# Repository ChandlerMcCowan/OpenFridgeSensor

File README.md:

# OpenFridgeSensor
Open source sensor and alarm system to remind you to close the fridge!

## Overview
I want to create a small sensor that lives in the fridge that can let you know when you accidentally leave the fridge door ajar. Most modern fridges come with this feature standard, but there are plenty of old fridges out there still keeping the beer cold. My goal is to have a low cost, battery powered sensor that connects wirelessy to a display that can be stuck to the fridge door with magnets. 

## Alert Types
Currently, I plan on using a small speaker to notify people that the door was left open. Other options could also include internet connectivity for when you might have just left the house after grabbing something out of the fridge. 

## Sensor Types
I plan on using a ambient light sensor to determine if the door was left open. These sensors are found in most smart phones to allow for automatically adjusting the screen's brightness. These sensors are low cost and come in small packages, perfect for a small device that shouldn't take up too much space in the fridge. 

Another idea is to add a temperature sensor to allow for alerts from loss of power or if the door is open but the light hasn't been switched on. This could be a simple thermistor, or it could be the popular DHT11 sensor, which would give humidity as well.

## Display Types
I want to explore the idea of using a small OLED or TFT display that attaches to the fridge door with magnets. This could show the current status of the sesnor, and flash for any alerts. Another idea is to include a user interface to allow for setting when to issue alerts, and what type of alerts. 

## Wireless Connectivity
I've looked at 433 Mhz in the ISM band to allow for wireless data transmission from the sensor inside the fridge to the display on the fridge door. There are plenty of small transmitter and reciever ICs. I expect to only need a transmitter for the in-fridge sensor, and just a reciever in the display. One area that I want to explore is the use of a PCB antenna instead of the common wire antenna. This will require some work, so I might fall back on the purchased antenna.

I want to explore using JSON objects to pass data from the sensor to the display.

## Battery Power
Both the sensor and the display should be batter powered. Maybe the display can have an IR sensor that detects when a person walks by to keep power consumption down. I expect to use a coincell for the in-fridge sensor, and maybe a 9V battery for the display. These will need some exploration to determine the best solution when the power consumption is calculated. 

## Enclosures
As usual, I will create some enclosures that can be 3D printed. One thing that might be interesting is to explore using epoxy or conformal coating to increase sensor robustness.

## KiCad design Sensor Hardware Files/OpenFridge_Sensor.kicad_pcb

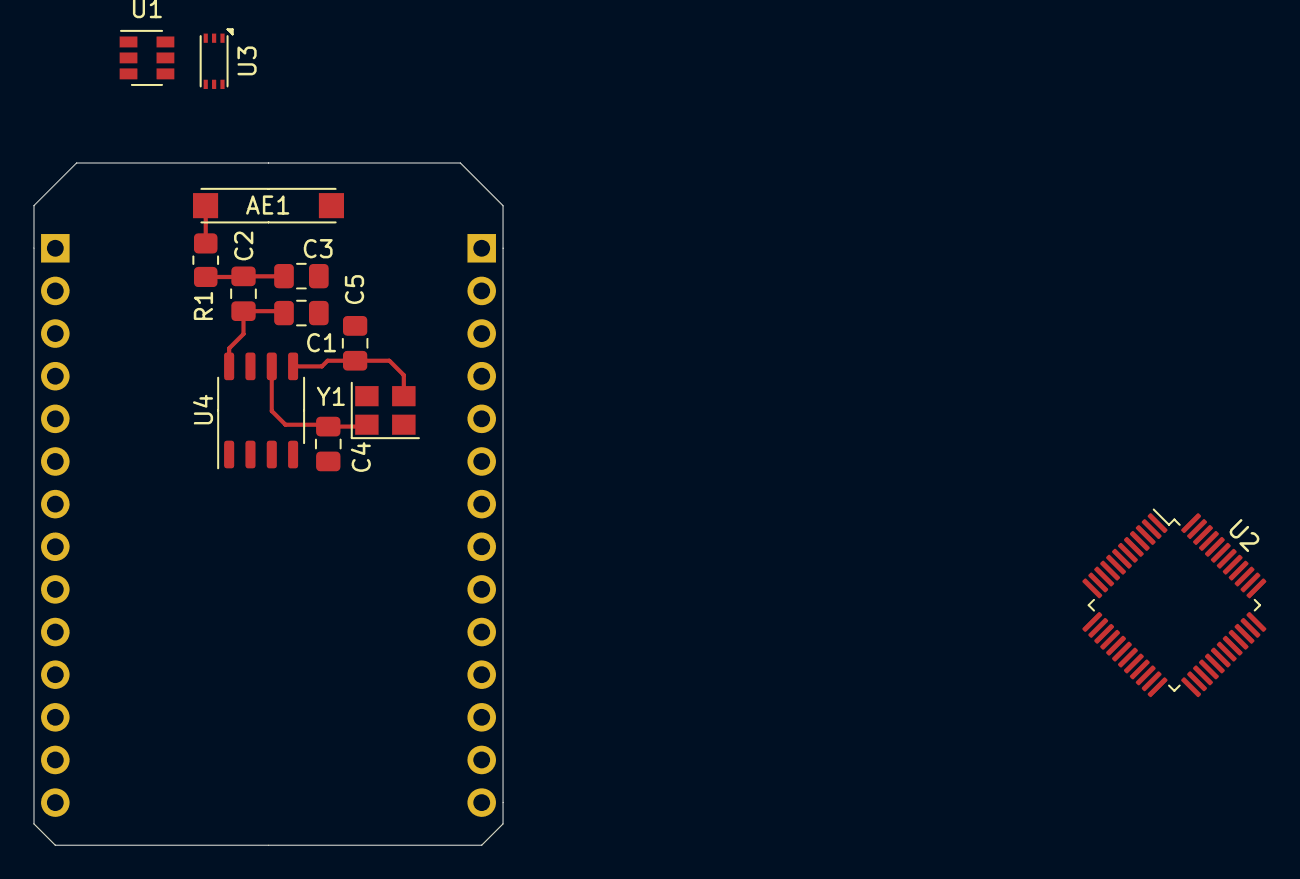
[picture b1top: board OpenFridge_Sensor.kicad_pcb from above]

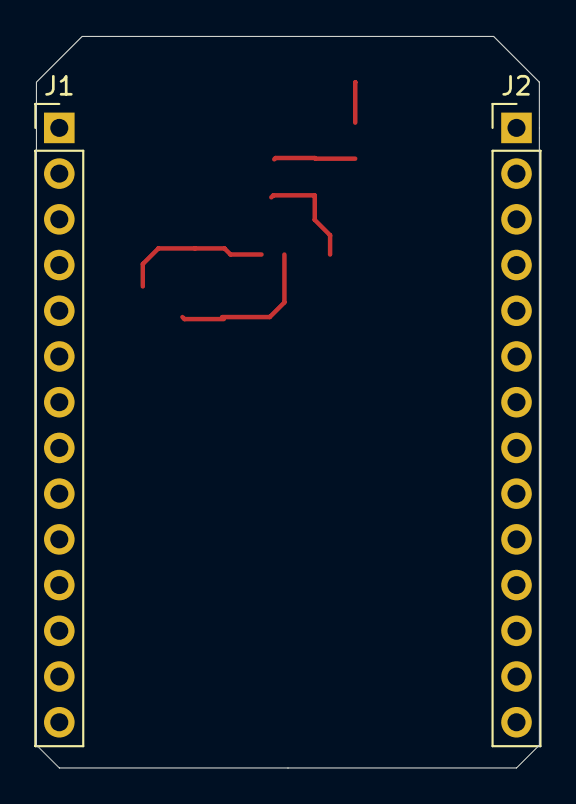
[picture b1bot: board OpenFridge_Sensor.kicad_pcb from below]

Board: 2 copper layers, 27.9 x 40.6 mm, 14 parts (2 on the bottom side), 8 nets.

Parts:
AE1: Antenna_Chip; RFANT8010080A3T
C1, C2, C3: C; C_0805_2012Metric_Pad1.18x1.45mm_HandSolder
C4, C5: 12pF; C_0805_2012Metric_Pad1.18x1.45mm_HandSolder
J1, J2: Conn_01x14; PinHeader_1x14_P2.54mm_Vertical
R1: R; R_0805_2012Metric_Pad1.20x1.40mm_HandSolder
U1: TMP101; SOT-23-6
U2: STM32F103C8Tx; LQFP-48_7x7mm_P0.5mm
U3: BH1730FVC; WSOF-6
U4: XN297LBW; SOP-8_3.9x4.9mm_P1.27mm
Y1: 16 MHz 12pF; Crystal_SMD_3225-4Pin_3.2x2.5mm

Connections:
GND: AE1.1, C1.1, C3.1, C4.1, C5.1, U4.7, Y1.2, Y1.4
I2C1_SCL: U1.1, U3.6
I2C1_SDA: U1.6, U3.4
unnamed: AE1.2, R1.1
unnamed: C1.2, C2.2, U4.8
unnamed: C2.1, C3.2, R1.2
unnamed: C4.2, U4.6, Y1.1
unnamed: C5.2, U4.5, Y1.3

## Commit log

2020-09-12 Add Sensor Hardware CAD files
2020-09-12 Add Display CAD Files
2020-09-12 Add empty Enclosure CAD Files
2020-09-12 Add License
2020-10-07 Add step up circuit
2020-10-07 Add ISM transceiver symbols and library
2020-10-08 Rename Antenna Connector Symbol
2020-10-14 Add Library Files
2020-10-14 Add BH1730 Symbol
2020-10-14 Add AT86RF231 Zigbee Transceiver
2020-10-14 Place AT86 RF Transceiver
2020-11-13 add page layout file
2020-11-13 change mcu to STM32F103C8T6
2020-11-13 add footprint library
2020-11-13 update bh17 footprint
2020-11-13 update footprints
2020-11-13 add chip antenna and board outline
2020-11-13 add XN297LBW to library
2020-11-13 change RF IC
2020-11-13 update RF IC passives
2020-11-13 update rf passives
